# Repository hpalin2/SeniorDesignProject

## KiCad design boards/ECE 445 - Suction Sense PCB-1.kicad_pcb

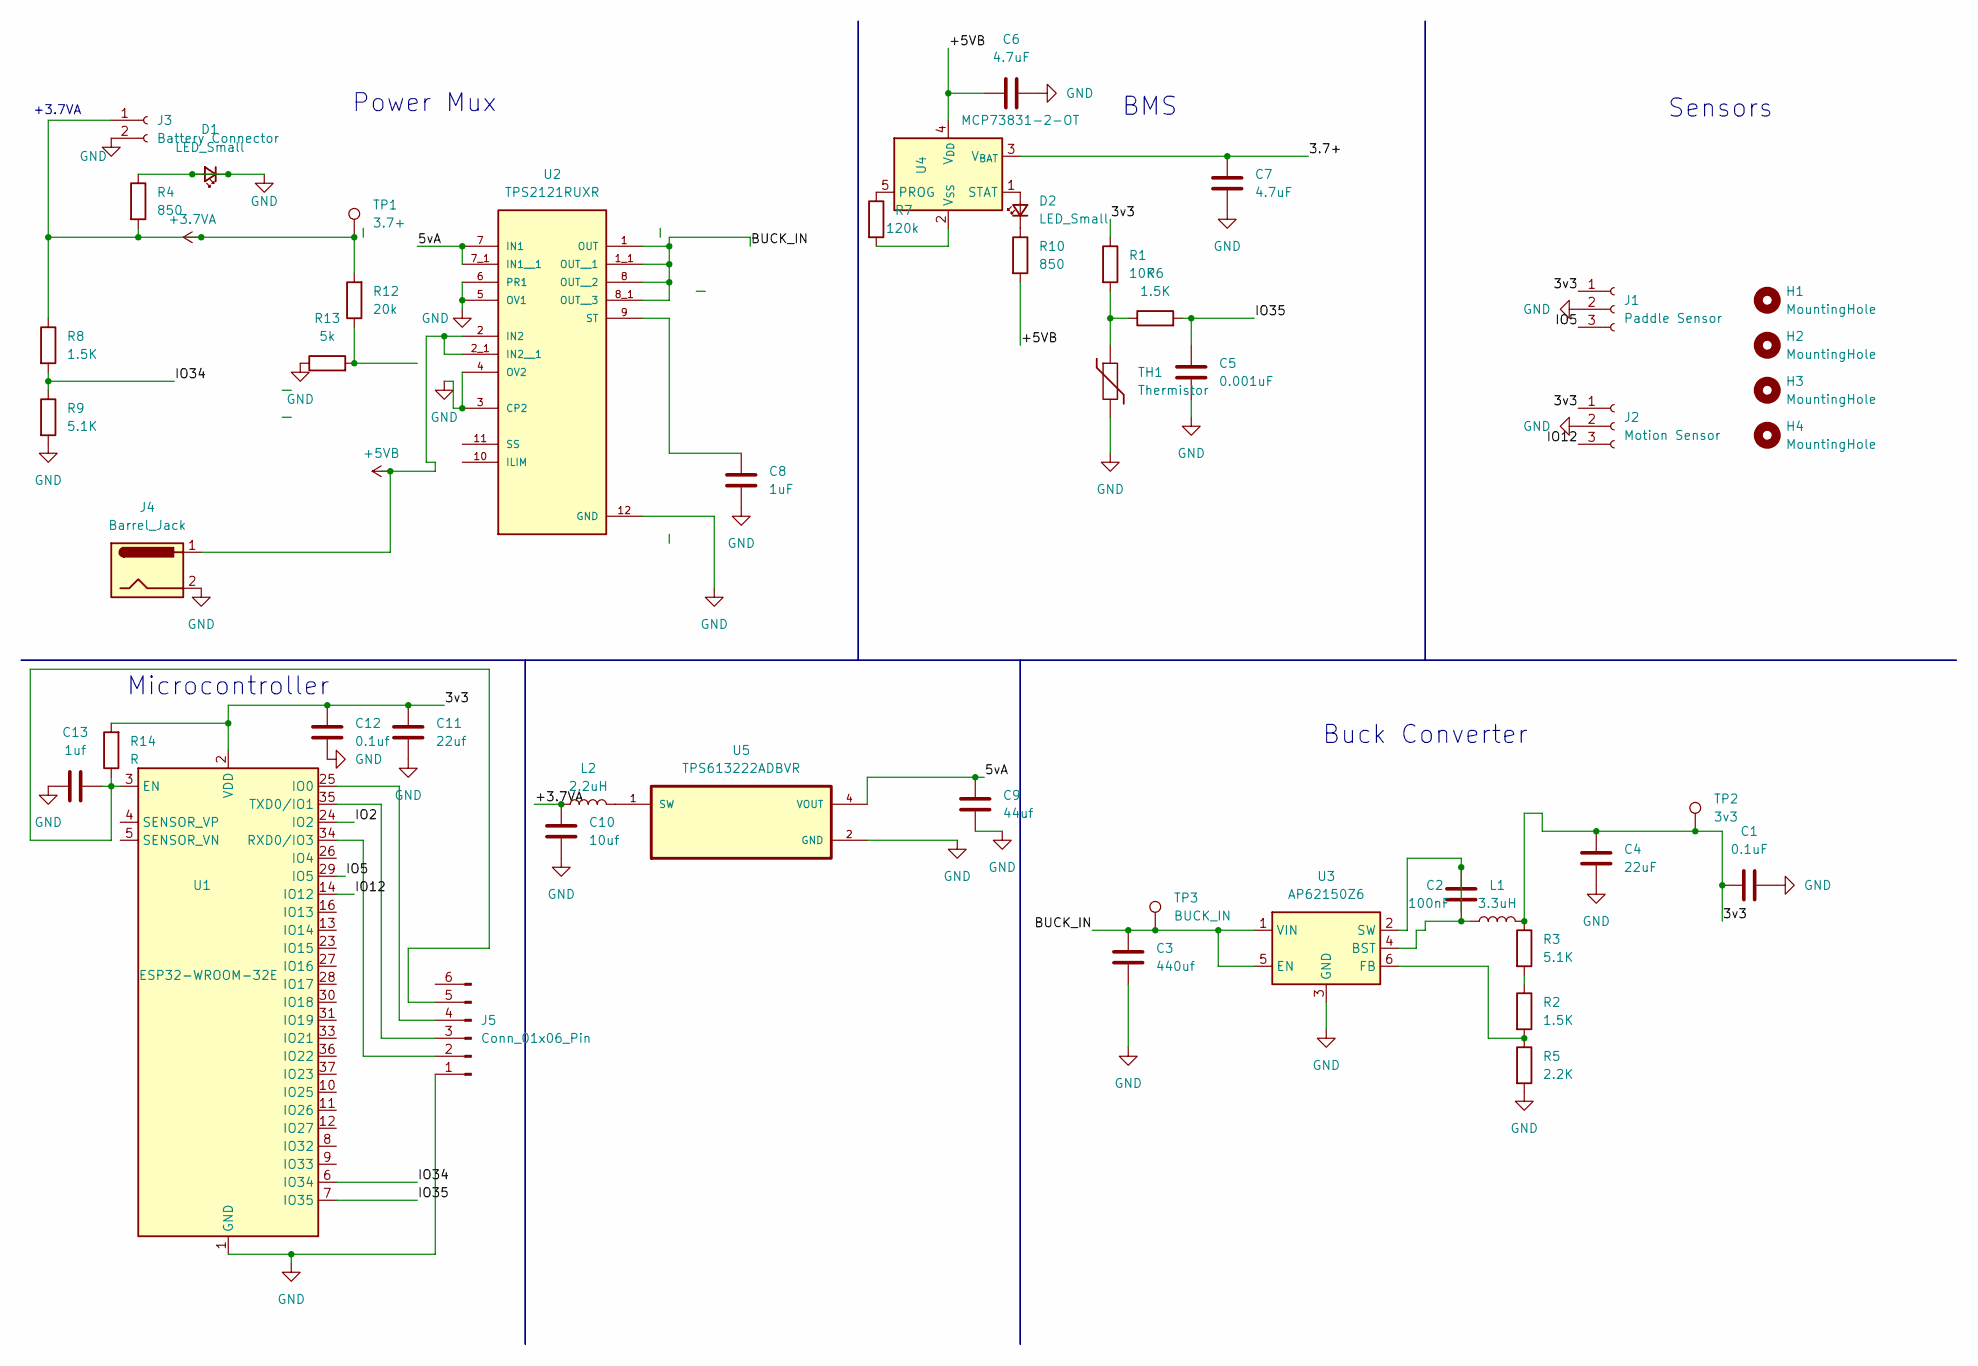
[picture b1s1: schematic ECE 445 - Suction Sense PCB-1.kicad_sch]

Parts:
C1: 0.1uF; CP_Elec_8x5.4
C2: 100nF; CP_Elec_8x5.4
C3: 440uf; CP_Elec_8x5.4
C4: 22uF; CP_Elec_8x5.4
C5: 0.001uF; CP_Elec_8x5.4
C6, C7: 4.7uF; C_0805_2012Metric_Pad1.18x1.45mm_HandSolder
C8: 1uF; C_0805_2012Metric_Pad1.18x1.45mm_HandSolder
C9: 44uf; C_0805_2012Metric_Pad1.18x1.45mm_HandSolder
C10: 10uf; C_0805_2012Metric_Pad1.18x1.45mm_HandSolder
C11: 22uf; C_0805_2012Metric_Pad1.18x1.45mm_HandSolder
C12: 0.1uf; C_0805_2012Metric_Pad1.18x1.45mm_HandSolder
C13: 1uf; C_0805_2012Metric_Pad1.18x1.45mm_HandSolder
D1, D2: LED_Small; LED_0805_2012Metric
H1, H2, H3, H4: MountingHole; MountingHole_3.2mm_M3
J1: Paddle Sensor; Molex_KK-254_AE-6410-03A_1x03_P2.54mm_Vertical
J2: Motion Sensor; Molex_KK-254_AE-6410-03A_1x03_P2.54mm_Vertical
J3: Battery Connector; BatteryHolder_Keystone_1057_1x2032
J4: Barrel_Jack; BarrelJack_CUI_PJ-036AH-SMT_Horizontal
J5: Conn_01x06_Pin; Molex_KK-396_A-41791-0006_1x06_P3.96mm_Vertical
L1: 3.3uH; L_Changjiang_FTC201655S
L2: 2.2uH; L_Changjiang_FTC201655S
R1: 10K; R_0508_1220Metric
R2, R6, R8: 1.5K; R_0508_1220Metric
R3, R9: 5.1K; R_0508_1220Metric
R4, R10: 850; R_0805_2012Metric_Pad1.20x1.40mm_HandSolder
R5: 2.2K; R_0508_1220Metric
R7: 120k; R_0805_2012Metric_Pad1.20x1.40mm_HandSolder
R12: 20k; R_0805_2012Metric_Pad1.20x1.40mm_HandSolder
R13: 5k; R_0805_2012Metric_Pad1.20x1.40mm_HandSolder
R14: R; R_0805_2012Metric_Pad1.20x1.40mm_HandSolder
TH1: Thermistor; R_0508_1220Metric
TP1: 3.7+; TestPoint_Pad_D2.0mm
TP2: 3v3; TestPoint_Pad_D2.0mm
TP3: BUCK_IN; TestPoint_Pad_D2.0mm
U1: ESP32-WROOM-32E; ESP32-WROOM-32D
U2: TPS2121RUXR; IC_TPS2121RUXR
U3: AP62150Z6; TSOT-23-6_HandSoldering
U4: MCP73831-2-OT; SOT-23-5
U5: TPS613222ADBVR; SOT95P280X145-5N

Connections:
+3.7VA: C10.1, J3.1, L2.1, R4.2, R8.1, R12.2, TP1.1
+5VB: C6.2, J4.1, R10.2, U2.2 (IN2), U2.2_1 (IN2__1), U4.4 (V_{DD})
/3.7+: C7.1, U4.3 (V_{BAT})
/3v3: C1.1, C4.1, C11.1, C12.1, J1.1, J2.1, L1.2, R1.1, R3.1, R14.2, TP2.1, U1.2 (VDD)
/5vA: C9.1, U2.7 (IN1), U2.7_1 (IN1__1), U5.4 (VOUT)
/BUCK_IN: C3.1, TP3.1, U2.1 (OUT), U2.1_1 (OUT__1), U2.8 (OUT__2), U2.8_1 (OUT__3), U3.1 (VIN), U3.5 (EN)
/IO2: U1.24 (IO2)
/IO5: J1.3, U1.29 (IO5)
/IO12: J2.3, U1.14 (IO12)
/IO34: R8.2, R9.1, U1.6 (IO34)
/IO35: C5.1, R6.2, U1.7 (IO35)
GND: C1.2, C3.2, C4.2, C5.2, C6.1, C7.2, C8.2, C9.2, C10.2, C11.2, C12.2, C13.1, D1.1 (K), D1.2 (A), J1.2, J2.2, J3.2, J4.2, J5.1, R4.1, R5.2, R9.2, R13.1, TH1.2, U1.1 (GND), U1.15 (GND), U1.38 (GND), U1.39 (GND), U2.3 (CP2), U2.4 (OV2), U2.5 (OV1), U2.6 (PR1), U2.12 (GND), U3.3 (GND), U5.2 (GND)
unnamed: D2.2 (A), U4.1 (STAT)
unnamed: D2.1 (K), R10.1
unnamed: J5.2, U1.34 (RXD0/IO3)
unnamed: J5.3, U1.35 (TXD0/IO1)
unnamed: J5.4, U1.25 (IO0)
unnamed: C13.2, J5.5, R14.1, U1.3 (EN)
unnamed: R1.2, R6.1, TH1.1
unnamed: R2.1, R3.2
unnamed: R12.1, R13.2
unnamed: C8.1, U2.9 (ST)
unnamed: C2.2, L1.1, U3.4 (BST)
unnamed: R2.2, R5.1, U3.6 (FB)
unnamed: C2.1, U3.2 (SW)
unnamed: R7.1, U4.5 (PROG)
unnamed: R7.2, U4.2 (V_{SS})
unnamed: L2.2, U5.1 (SW)

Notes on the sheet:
+3.7VA
BMS
Power Mux
Microcontroller
Buck Converter
Sensors

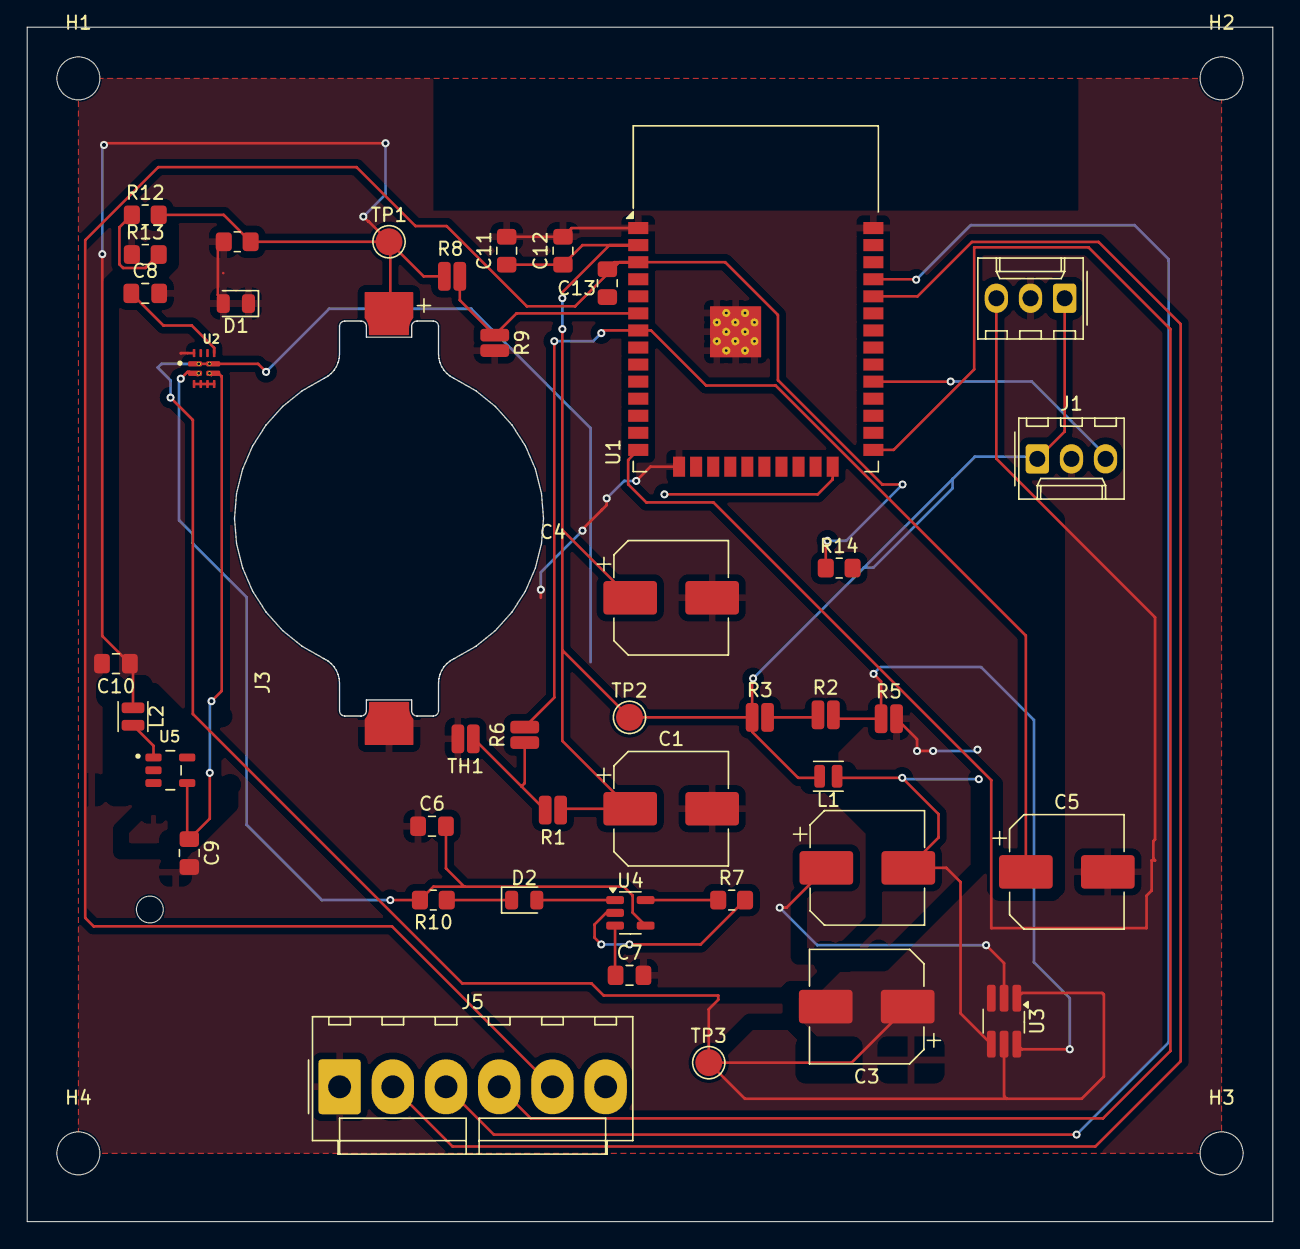
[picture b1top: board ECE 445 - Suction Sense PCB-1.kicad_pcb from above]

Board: 2 copper layers, 92.7 x 88.8 mm, 48 parts (1 on the bottom side), 27 nets.

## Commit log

2025-09-16 Add Jeremy's Lab Notebook XML file
2025-09-16 Rename journal to lab notebook
2025-09-16 Add Suley's Lab Notebook XML file
2025-09-24 Setting up repo
2025-09-24 adding new project for pcb on the repository
2025-09-24 suley smells
2025-09-24 Adding Jeremy's notebook
2025-09-26 Worked on schematic - jeremy
2025-09-26 finished buck
2025-09-26 Added Thursday Journal Entry - Jeremy
2025-09-26 Finished PCB Schematic
2025-09-26 Jeremy update notebook
2025-09-26 adding changes and updated pcb just needs routing
2025-09-28 routed
2025-09-30 adding changes to the pcb finishing connections with power mux
2025-10-02 Changed voltage divider for powermux and also modified the buck converter Fb resistor network - Jeremy
2025-10-03 finsih adding charging
2025-10-03 adding changes to the journal and pcb design, as well as adding the LED gnd connection on schematic
2025-10-03 adding changes need to update pcb with new package
2025-10-04 Jeremy - 10/4 changes
2025-10-05 added gnd pour
2025-10-06 routed with new footprint
2025-10-08 update journal and crow starter code
2025-10-08 adding new changes to pcb
2025-10-08 adding changes to lab notebook
2025-10-10 Update README with design doc progress
    Added a new entry about the design doc and project schedule.
2025-10-11 Jeremy journal 10/10
2025-10-12 added journal for this weekend
2025-10-12 added boost converter
2025-10-13 added lined
2025-10-15 Simple crow app running
2025-10-15 Fix typos and update project timeline in README
    Corrected typos and added a new entry for software requirements.
2025-10-15 10/15 meeting
2025-10-16 forgot to submit my changes to notebook this week, my bad
2025-10-16 Jeremy notebook update 10.15
2025-10-16 adding environment to go to my next pc
2025-10-16 adding changes to my notebook and adding the code I used to setup a basic html server using crow framework. Followed their instructions, couldn't get the mustache variable thing tho.
2025-10-17 adding new environment yml
2025-10-17 adding our webapp and changes to my readme
2025-10-18 adding new changes to the webapp to pull from an sqlite database
2025-10-18 adding my changes to webapp now we have a working database that pulls current OR schedules and updates our website
2025-10-19 Jeremy notebook update 10/18
2025-10-19 Static website running on mac - Jeremy
2025-10-22 Update journal-Jeremy
2025-10-22 adding changes to my notebook
2025-10-23 ESP32 MQTT test working - Jeremy
2025-10-24 Breadboard demo 2 code
2025-10-24 adding
2025-10-29 adding work I did today and yesterday
2025-10-31 changed schematic and baord
2025-10-31 adding journal entry
2025-10-31 Refactored codebase
2025-10-31 Save build cmd
2025-11-01 Mqtt_ingestor
2025-11-04 ESP32 updates application
2025-11-04 adding changes to journal
2025-11-05 added changes to mqtt and repo that changed how our database was initialized as well as got it to work on my pc by adding catch to mqtt
2025-11-05 edit schematic
2025-11-07 Raspberry pi config
2025-11-07 E2E Pi working
2025-11-07 Works with pi touchscreen
2025-11-07 notebook update
2025-11-07 got stuff somewhat working
2025-11-07 Adding fixed working UI
2025-11-09 new baord
2025-11-09 better footprint for boost
2025-11-09 new upadtes to board
2025-11-13 Update README with progress entry for 11/13/2025
    Added a new entry for 11/13/2025 detailing coordination with the machine shop and progress on the test stand.
2025-11-13 Update README with project timeline and progress
    Added detailed project timeline with updates on design, components, and issues encountered.
2025-11-16 Jeremy's jouranl
2025-11-16 adding changes to readme that I didn't add other day
2025-11-16 adding changes making our OR occupancy be a boolean rather then text
2025-11-16 adding changes to me notebook
2025-11-16 Motion Sensor code for esp32
2025-11-19 Jeremy 11/19
2025-11-20 Working Web App Code With Motion
2025-11-20 Jeremy - 11/20
2025-11-20 Code + Journal cleanup - Jeremy 11/20
2025-12-01 Update project timeline with recent progress entries
    Added additional entries to the project timeline, detailing progress and issues encountered during the PCB design and testing phases, including component selection and circuit adjustments.
2025-12-01 Revised notebook to follow the specifications and format required by class
    Updated the README to reflect project progress, objectives, work completed, reflections, and next steps for multiple dates.
2025-12-01 Format fixes
    Updated README with detailed notes on project progress, objectives, and work completed.
2025-12-02 JS UI update
2025-12-02 data
2025-12-03 Journal - Jeremy
2025-12-09 Revise README with project timeline and updates
    Updated the README to reflect the project's progress and detailed documentation of design decisions, issues encountered, and resolutions from September to December 2025.
2025-12-09 Revise README with project milestones and updates
    Updated the README with detailed project logs and milestones, documenting the progress and challenges faced during the PCB design and integration process.
2025-12-09 Revise README with project progress and updates
    Updated the README to include detailed logs of project milestones, issues encountered, and resolutions from initial part sourcing to final verification and testing.
